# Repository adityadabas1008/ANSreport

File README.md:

# ANSreport

Hello there! Welcome to the ANSreport repository.

This repository is a combined work of the students of the course "Analoge Schaltungen" from the Hochschule Bremen, under the mentorship of **Prof. Dr. Mirco Meiners**.

The contributors are:
- Aditya Dabas
- Adrian Jauch
- Mohamad Wehbi

What you see here is a quarto report of a project from the 'Texas Instruments Analog Circuits Lab Kit' manual.

The project aimed at building deeper understanding of analog circuits using the universal biquad filter design.
Here, we implemented the second order biquad filter in three different stages:
1. **The theory level**: Here, we explored the ideal world of Electronics by simulating the circuit in KiCAD.
2. **Filter on a discrete circuit design**: After that the circuit was build on the lab board of ASLK using jumper wires, was somewhat imperfect, but still worked.
3. **The integrated PCB Design**: Then we wanted to explore the PCB design of the circuit, so we designed the biquad filter on a PCB, in a compact form and checked the functionality in the lab, we also tried to expand the circuit by adding another order to our second order filter, by cascading a second order filter to another butterworth filter to get a third order filter and a cleaner curve.

Now, its upto you to explore the interesting results we got in the ideal world and the real world of electronics.
Another question would be, were we able to successfully cascade the second order filter to a third order filter to get the butterworth output ? was it successful on the compact PCB we designed ?

Run the report to find out!

Please note that the report is in German, as it was a project for a German course.

## How to run the report
1. Clone the repository as it is.
2. Choose the editor of your choice, e.g. [VSCode](https://code.visualstudio.com/).
3. Make sure you have [quarto](https://quarto.org/docs/get-started/) installed.
4. Just render the index.qmd file in the editor.

Voila! You should see the report in your browser.

Thank you for your interest in our project!

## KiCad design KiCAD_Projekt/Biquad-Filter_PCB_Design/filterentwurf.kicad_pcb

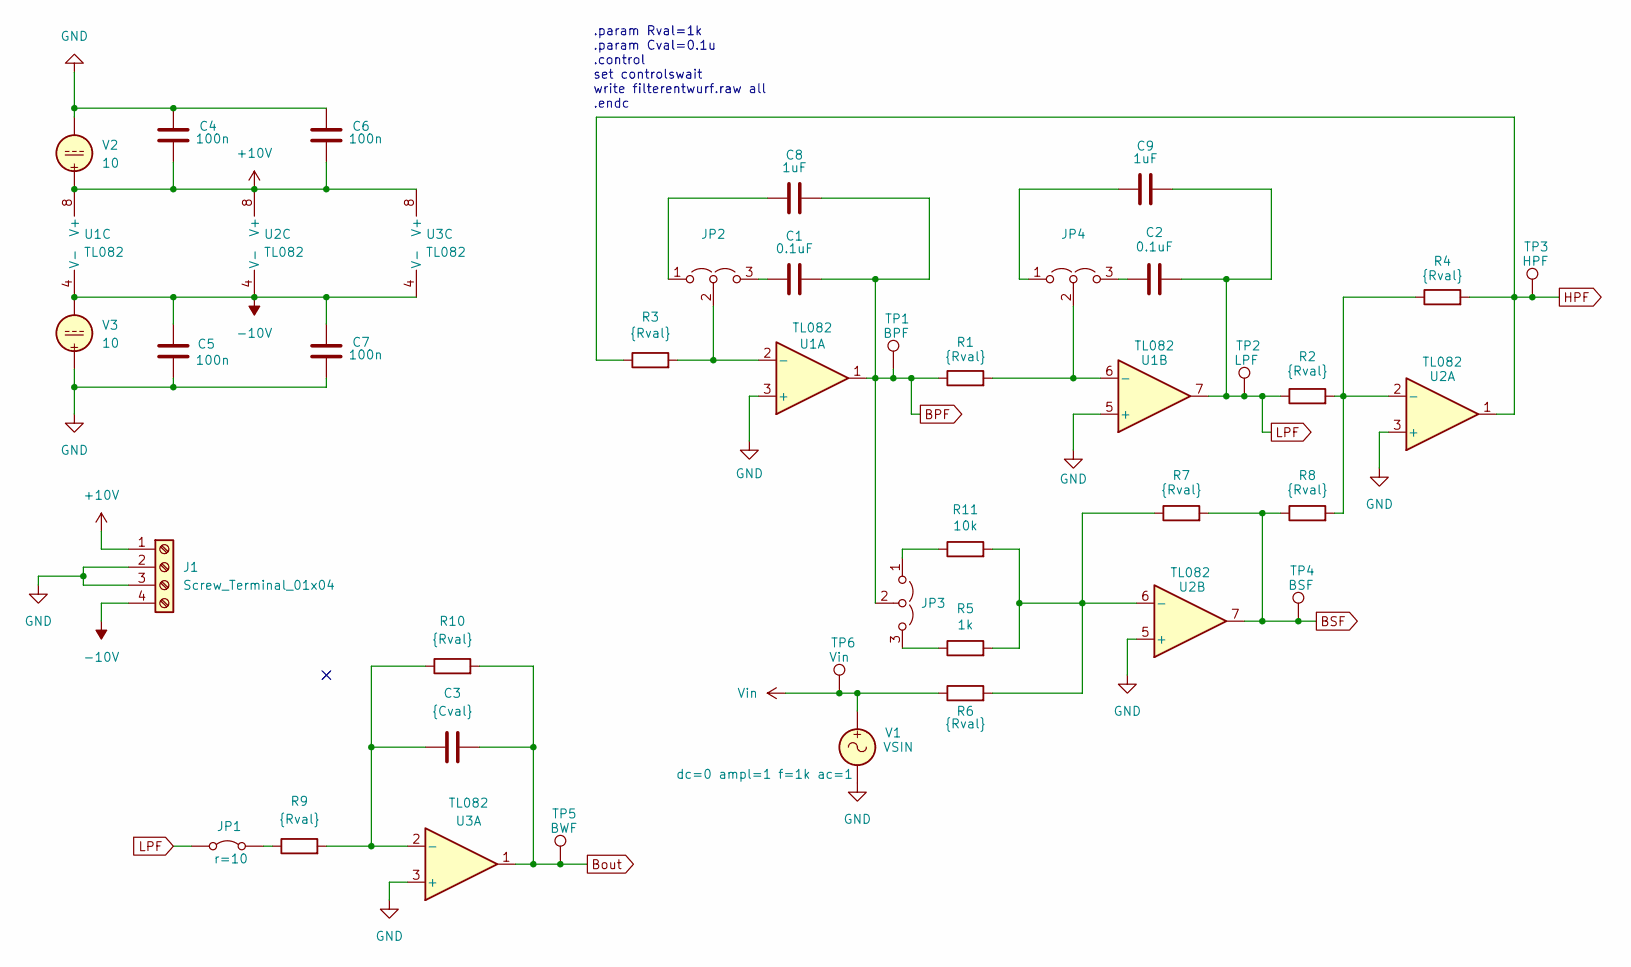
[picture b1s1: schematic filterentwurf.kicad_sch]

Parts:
C1, C2: 0.1uF; C_Disc_D5.0mm_W2.5mm_P5.00mm
C3: {Cval}; C_Disc_D5.0mm_W2.5mm_P5.00mm
C4, C5, C6, C7: 100n; C_Disc_D5.0mm_W2.5mm_P5.00mm
C8, C9: 1uF; C_Disc_D5.0mm_W2.5mm_P5.00mm
J1: Screw_Terminal_01x04; TerminalBlock_Phoenix_PT-1,5-4-5.0-H_1x04_P5.00mm_Horizontal
JP1: r=10; PinHeader_1x02_P2.54mm_Vertical
JP2, JP3, JP4: Jumper_3_Open; PinHeader_1x03_P2.54mm_Vertical
R1, R2, R3, R4, R6, R7, R8, R9, R10: {Rval}; R_Axial_DIN0309_L9.0mm_D3.2mm_P12.70mm_Horizontal
R5: 1k; R_Axial_DIN0309_L9.0mm_D3.2mm_P12.70mm_Horizontal
R11: 10k; R_Axial_DIN0309_L9.0mm_D3.2mm_P12.70mm_Horizontal
TP1: BPF; TestPoint
TP2: LPF; TestPoint
TP3: HPF; TestPoint
TP4: BSF; TestPoint
TP5: BWF; TestPoint
TP6: Vin; TestPoint
U1, U2, U3: TL082; CERDIP-8_W7.62mm_SideBrazed
V1: VSIN
V2, V3: 10

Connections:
+10V: C4.2, C6.2, J1.1, U1.8 (V+), U2.8 (V+), U3.8 (V+), V2.1
-10V: C5.1, C7.1, J1.4, U1.4 (V-), U2.4 (V-), U3.4 (V-), V3.2
BPF: C1.2, C8.2, JP3.2 (C), R1.1, TP1.1, U1.1
BSF: R7.2, R8.1, TP4.1, U2.7
Bout: C3.1, R10.2, TP5.1, U3.1
GND: C4.1, C5.2, C6.1, C7.2, J1.2, J1.3, U1.3 (+), U1.5 (+), U2.3 (+), U2.5 (+), U3.3 (+), V1.2, V2.2, V3.1
HPF: R3.1, R4.2, TP3.1, U2.1
LPF: C2.2, C9.2, JP1.1 (A), R2.1, TP2.1, U1.7
unnamed: JP1.2 (B), R9.1
unnamed: C8.1, JP2.1 (A)
unnamed: C1.1, JP2.3 (B)
unnamed: JP2.2 (C), R3.2, U1.2 (-)
unnamed: JP3.1 (A), R11.1
unnamed: JP3.3 (B), R5.1
unnamed: C9.1, JP4.1 (A)
unnamed: C2.1, JP4.3 (B)
unnamed: JP4.2 (C), R1.2, U1.6 (-)
unnamed: R2.2, R4.1, R8.2, U2.2 (-)
unnamed: R5.2, R6.2, R7.1, R11.2, U2.6 (-)
unnamed: C3.2, R9.2, R10.1, U3.2 (-)
Vin: R6.1, TP6.1, V1.1

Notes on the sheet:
.param Rval=1k .param Cval=0.1u .control set controlswait write filterentwurf.raw all .endc

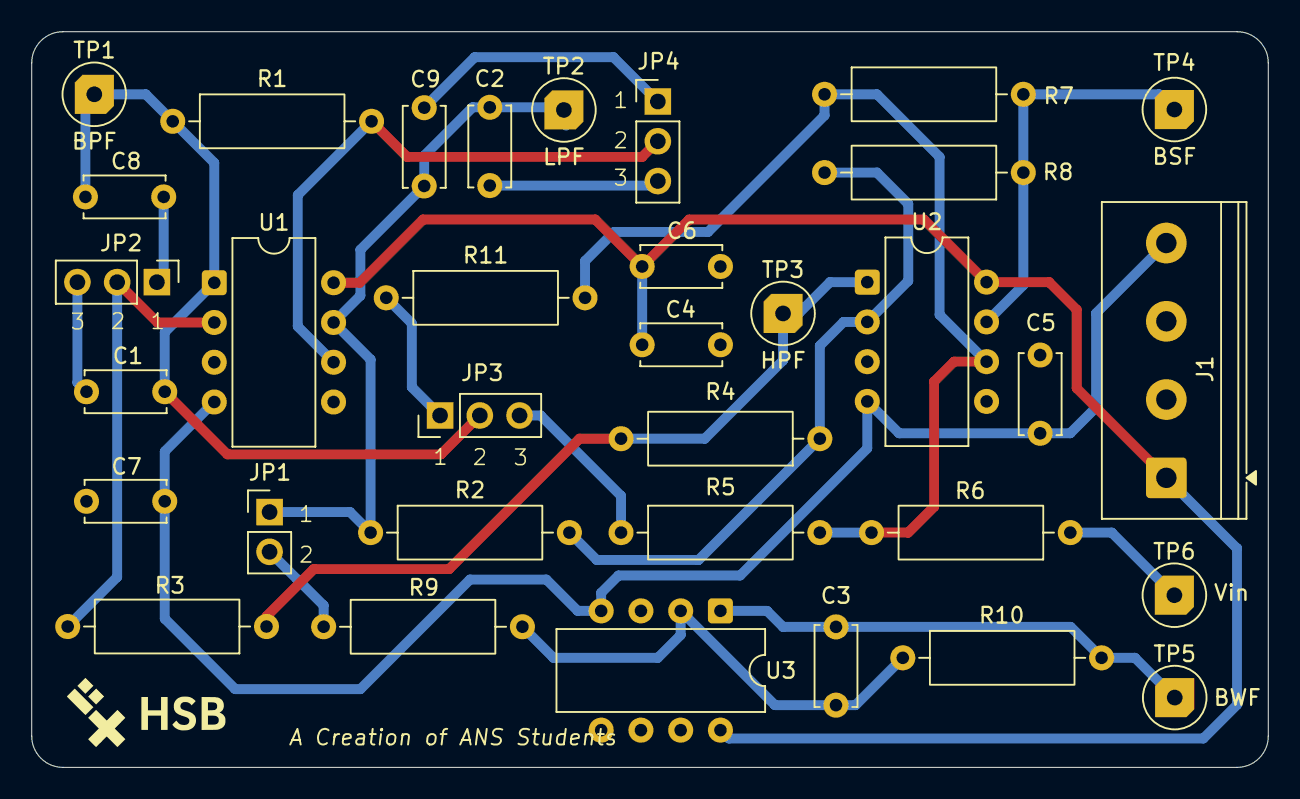
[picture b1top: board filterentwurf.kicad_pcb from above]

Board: 2 copper layers, 79.0 x 47.0 mm, 34 parts (0 on the bottom side), 21 nets.

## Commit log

2025-06-24 README update
2025-06-24 Initial commit: added the non-structured report
2025-06-24 Read GIT_WORKFLOW to understand GIT
2025-06-24 Readme file updated
2025-06-29 Updated the structure of lab report
2025-06-29 Updated the structure and contents of Report
2025-06-30 Structure and contents updated
2025-06-30 Added Lab measurements
2025-07-01 Initializing gh-pages branch
2025-07-01 Built site for gh-pages
2025-07-01 Nur html, kein pdf
2025-07-01 Updated measurements
2025-07-01 Added the updated measurments
2025-07-01 Added new Plots
2025-07-08 Edited the file butter
2025-07-08 PCB measurements added
2025-07-13 Ref Update
2025-07-13 Remove deleted Butter files
2025-07-13 Gliederung festgelegt
2025-07-15 Updated files
2025-07-15 Butterworth simulation measurements added
2025-07-15 Platine vs Realaufbau plots added
2025-07-15 Platine vs Simulation plot added
2025-07-17 Neue Gliedrungsvorschlag
2025-07-18 index
2025-07-18 readme
2025-07-18 progress update
2025-07-18 Änderung
2025-07-18 Änderung theorie teil
2025-07-19 Änderungen
2025-07-19 Bericht Änderungen
2025-07-19 working
2025-07-19 progress
2025-07-20 Änderung Bericht
2025-07-20 Änderung an Gliederung datei
2025-07-20 Data added
2025-07-20 done
2025-07-20 apply changes
2025-07-20 Probe
2025-07-20 donee
2025-07-20 asdd
2025-07-20 final
2025-07-20 Fertig
2025-07-21 KiCAD Projekt
2025-07-21 Bericht und KiCAD angepasst
2025-08-19 untracked files
